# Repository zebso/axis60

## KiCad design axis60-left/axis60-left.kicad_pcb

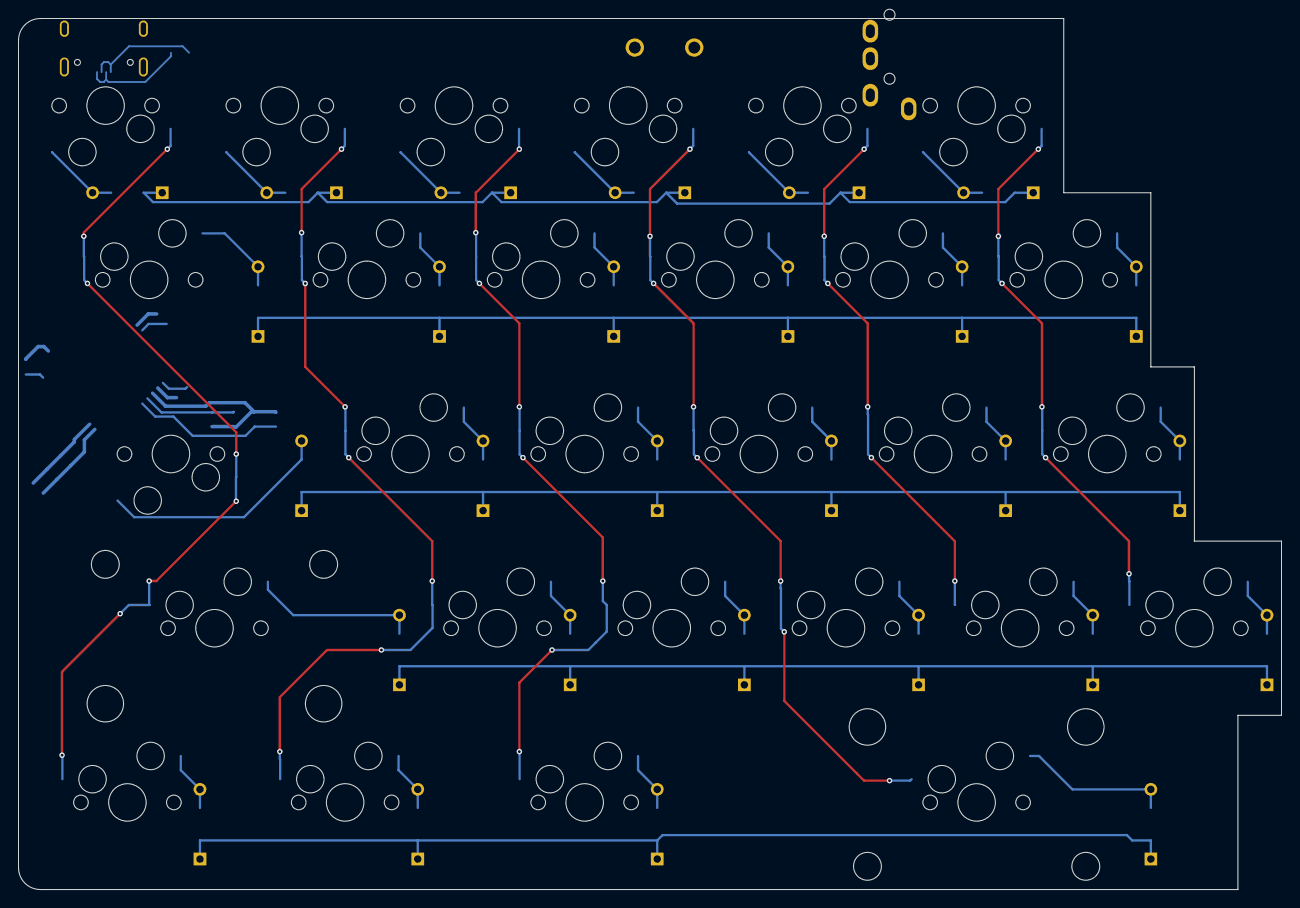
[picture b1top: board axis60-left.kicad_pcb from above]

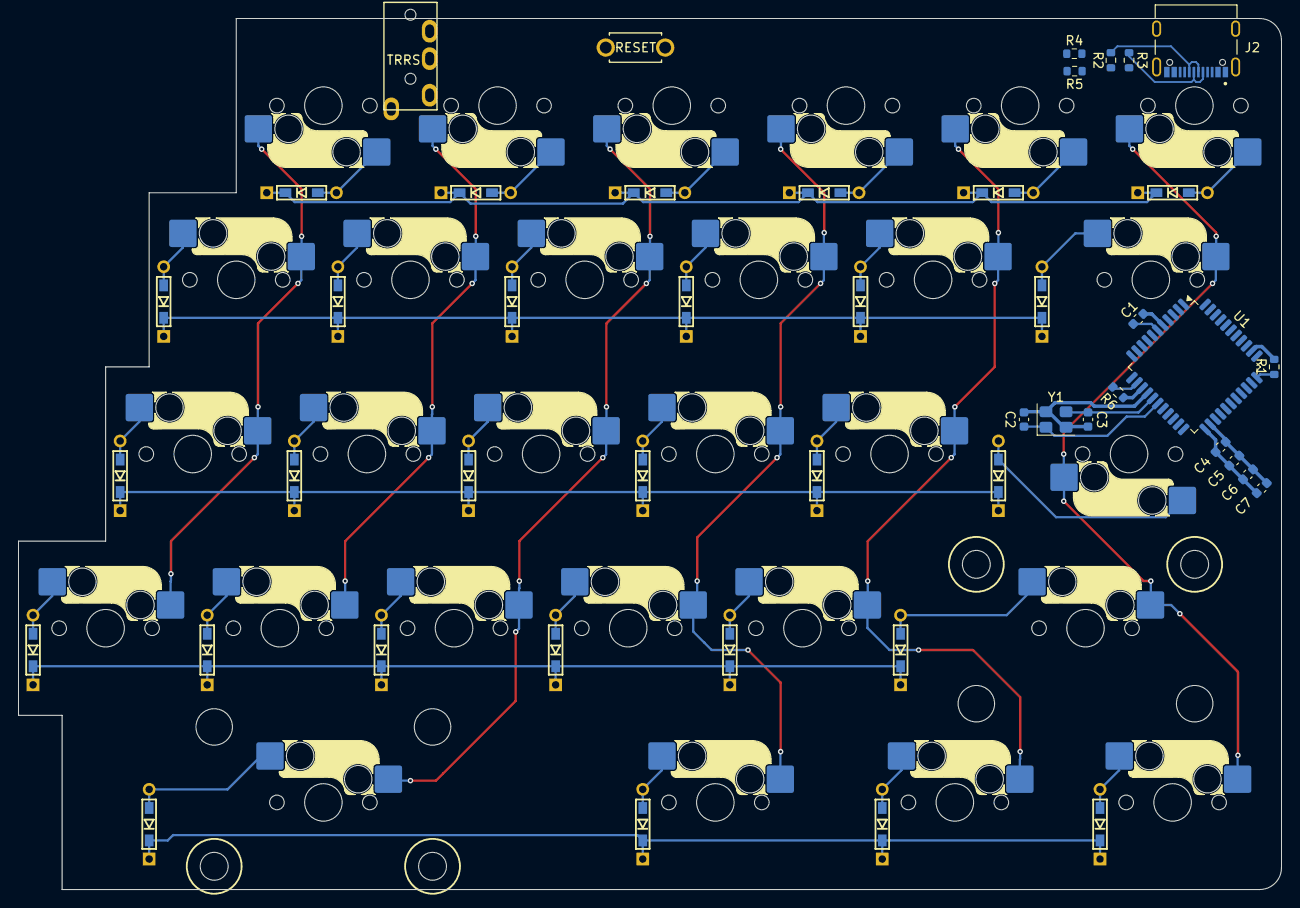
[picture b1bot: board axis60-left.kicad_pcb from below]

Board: 2 copper layers, 138.1 x 95.2 mm, 74 parts (18 on the bottom side), 53 nets.

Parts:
C1: 1uF; C_0603_1608Metric
C2, C3: 22pF; C_0603_1608Metric
C4: 10uF; C_0603_1608Metric
C5, C6, C7: 0.1uF; C_0603_1608Metric
D1, D2, D3, D4, D5, D6, D7, D8, D9, D10, D11, D12, D13, D14, D15, D16, D17, D18, D19, D20, D21, D22, D23, D24, D25, D26, D27, D28: 1N4148; D3_TH_SMD
J2: 5077CR-16SMC2-BK-TR; Usb_C_NELTRON_5077CR-16SMC2-BK-TR
J4: MJ-4PP-9
R1, R6: 10k; R_0603_1608Metric
R2, R3: 22; R_0603_1608Metric
R4, R5: 5.1k; R_0603_1608Metric
SW1: esc; CherryMX_Hotswap_via_1U
SW2: 1; CherryMX_Hotswap_via_1U
SW3: 2; CherryMX_Hotswap_via_1U
SW4: 3; CherryMX_Hotswap_via_1U
SW5: 4; CherryMX_Hotswap_via_1U
SW6: 5; CherryMX_Hotswap_via_1U
SW7: Tab; CherryMX_Hotswap_via_1.5U
SW8: Q; CherryMX_Hotswap_via_1U
SW9: W; CherryMX_Hotswap_via_1U
SW10: E; CherryMX_Hotswap_via_1U
SW11: R; CherryMX_Hotswap_via_1U
SW12: T; CherryMX_Hotswap_via_1U
SW13: Ctrl; CherryMX_Hotswap_via_1.75U
SW14: A; CherryMX_Hotswap_via_1U
SW15: S; CherryMX_Hotswap_via_1U
SW16: D; CherryMX_Hotswap_via_1U
SW17: F; CherryMX_Hotswap_via_1U
SW18: G; CherryMX_Hotswap_via_1U
SW19: L-Shift; CherryMX_Hotswap_via_2.25U
SW20: Z; CherryMX_Hotswap_via_1U
SW21: X; CherryMX_Hotswap_via_1U
SW22: C; CherryMX_Hotswap_via_1U
SW23: V; CherryMX_Hotswap_via_1U
SW24: B; CherryMX_Hotswap_via_1U
SW25: Ctrl; CherryMX_Hotswap_via_1.25U
SW26: Win; CherryMX_Hotswap_via_1.25U
SW27: Alt; CherryMX_Hotswap_via_1.5U
SW28: Space; CherryMX_Hotswap_via_3U
SW29: Reset SW; ResetSW
U1: ATmega32U4-A; TQFP-44_10x10mm_P0.8mm
Y1: 16MHz; Crystal_SMD_3225-4Pin_3.2x2.5mm

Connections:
D+: J2.A6 (DP1), J2.B6 (DP2), R2.1
D-: J2.A7 (DN1), J2.B7 (DN2), R3.1
GND: C1.1, C2.1, C3.1, C4.2, C5.2, C6.2, C7.2, J2.A1_B12 (GND), J2.B1_A12 (GND), J2.S1 (SHIELD), J2.S2 (SHIELD), J2.S3 (SHIELD), J2.S4 (SHIELD), J4.C, R1.2, R4.1, R5.2, SW29.2, U1.5 (UGND), U1.15 (GND), U1.23 (GND), U1.35 (GND), U1.43 (GND), Y1.2, Y1.4
unnamed: D1.2 (A), SW1.2
unnamed: D2.2 (A), SW2.2
unnamed: D3.2 (A), SW3.2
unnamed: D4.2 (A), SW4.2
unnamed: D5.2 (A), SW5.2
unnamed: D6.2 (A), SW6.2
unnamed: D7.2 (A), SW7.2
unnamed: D8.2 (A), SW8.2
unnamed: D9.2 (A), SW9.2
unnamed: D10.2 (A), SW10.2
unnamed: D11.2 (A), SW11.2
unnamed: D12.2 (A), SW12.2
unnamed: D13.2 (A), SW13.2
unnamed: D14.2 (A), SW14.2
unnamed: D15.2 (A), SW15.2
unnamed: D16.2 (A), SW16.2
unnamed: D17.2 (A), SW17.2
unnamed: D18.2 (A), SW18.2
unnamed: D19.2 (A), SW19.2
unnamed: D20.2 (A), SW20.2
unnamed: D21.2 (A), SW21.2
unnamed: D22.2 (A), SW22.2
unnamed: D23.2 (A), SW23.2
unnamed: D24.2 (A), SW24.2
unnamed: D25.2 (A), SW25.2
unnamed: D26.2 (A), SW26.2
unnamed: D27.2 (A), SW27.2
unnamed: D28.2 (A), SW28.2
unnamed: J2.A5 (CC1), R4.2
unnamed: J2.B5 (CC2), R5.1
unnamed: R2.2, U1.4 (D+)
unnamed: R3.2, U1.3 (D-)
unnamed: C1.2, U1.6 (UCAP)
unnamed: R1.1, U1.33 (~HWB/PE2)
Reset: R6.2, SW29.1, U1.13 (~RESET)
VCC: C4.1, C5.1, C6.1, C7.1, J2.A4_B9 (VBUS), J2.B4_A9 (VBUS), J4.D, R6.1, U1.2 (UVCC), U1.7 (VBUS), U1.14 (VCC), U1.24 (AVCC), U1.34 (VCC), U1.44 (AVCC)
XTAL1: C2.2, U1.17 (XTAL1), Y1.1
XTAL2: C3.2, U1.16 (XTAL2), Y1.3
col0: SW1.1, SW7.1, SW13.1, SW19.1, SW25.1
col1: SW2.1, SW8.1, SW14.1, SW20.1, SW26.1
col2: SW3.1, SW9.1, SW15.1, SW21.1, SW27.1
col3: SW4.1, SW10.1, SW16.1, SW22.1, SW28.1
col4: SW5.1, SW11.1, SW17.1, SW23.1
col5: SW6.1, SW12.1, SW18.1, SW24.1
data: J4.B, U1.20 (PD2)
row0: D1.1 (K), D2.1 (K), D3.1 (K), D4.1 (K), D5.1 (K), D6.1 (K)
row1: D7.1 (K), D8.1 (K), D9.1 (K), D10.1 (K), D11.1 (K), D12.1 (K)
row2: D13.1 (K), D14.1 (K), D15.1 (K), D16.1 (K), D17.1 (K), D18.1 (K)
row3: D19.1 (K), D20.1 (K), D21.1 (K), D22.1 (K), D23.1 (K), D24.1 (K)
row4: D25.1 (K), D26.1 (K), D27.1 (K), D28.1 (K)

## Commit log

2025-08-31 created KiCad project
2025-08-31 created left board's symbol
2025-09-10 updated PCB layout
